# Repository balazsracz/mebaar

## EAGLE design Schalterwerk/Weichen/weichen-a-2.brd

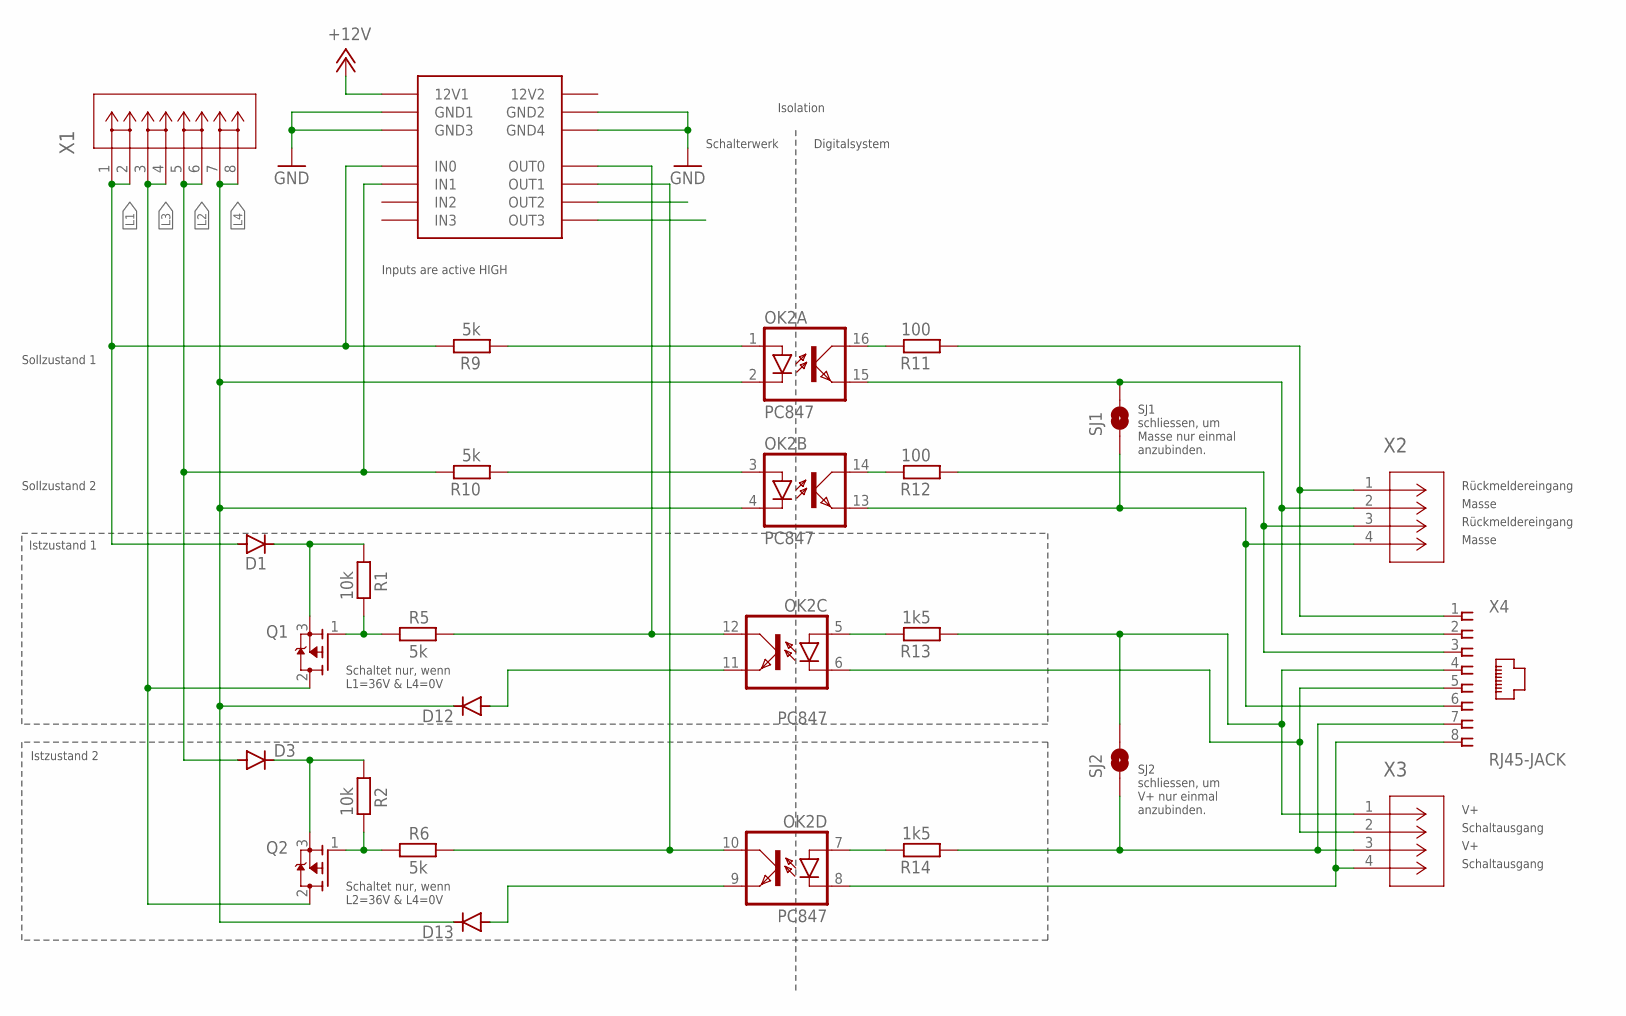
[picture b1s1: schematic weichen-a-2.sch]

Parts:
D1, D3: DIODE-DO214AC; DO214AC
D12, D13: DIODE-MINIMELF; MINIMELF
OK2: PC847; DIL16
Q1, Q2: P-MOSFET; DPAK-2
R1, R2: 10k; R0805
R5, R6, R9, R10: 5k; R0805
R11, R12: 100; R0805
R13, R14: 1k5; R0805
SJ1, SJ2: SJRND2; SJ_RND2
X1: PHNX_4P_508CONN_1017493; PHNX_4P_508
X2, X3: PHNX_4P_350CONN_1984989_PXC; PHNX_4P_350
X4: RJ45-JACK; RJ45-PULSE-E5J88
X5: IO-HAT; IOBOARD

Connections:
12V2: X5.P$22 (12V2)
+12V: X5.P$1 (12V1)
GND: X5.P$2 (GND1), X5.P$11 (GND3), X5.P$12 (GND4), X5.P$21 (GND2)
L1: D1.A, R9.2, X1.1, X1.2, X5.P$3 (IN0)
L2: D3.A, R10.2, X1.5, X1.6, X5.P$4 (IN1)
L3: Q1.2 (D), Q2.2 (D), X1.3, X1.4
L4: D12.C, D13.C, OK2.2 (C), OK2.4 (C), X1.7, X1.8
unnamed: D3.C, Q2.3 (S), R2.1
unnamed: OK2.1 (A), R9.1
unnamed: R11.1, X2.1, X4.1
unnamed: OK2.15 (EMIT), SJ1.P$2 (2), X2.2, X4.2
unnamed: OK2.5 (A), R13.2
unnamed: R12.1, X2.3, X4.3
unnamed: OK2.3 (A), R10.1
unnamed: OK2.7 (A), R14.2
unnamed: Q1.1 (G), R1.2, R5.1
unnamed: Q2.1 (G), R2.2, R6.1
unnamed: D1.C, Q1.3 (S), R1.1
unnamed: OK2.6 (C), X3.2, X4.5
unnamed: OK2.12 (COL), R5.2, X5.P$20 (OUT0)
unnamed: OK2.10 (COL), R6.2, X5.P$19 (OUT1)
unnamed: D12.A, OK2.11 (EMIT)
unnamed: OK2.16 (COL), R11.2
unnamed: OK2.13 (EMIT), SJ1.P$1 (1), X2.4, X4.6
unnamed: OK2.14 (COL), R12.2
unnamed: D13.A, OK2.9 (EMIT)
unnamed: R13.1, SJ2.P$2 (2), X3.1, X4.4
unnamed: R14.1, SJ2.P$1 (1), X3.3, X4.7
unnamed: OK2.8 (C), X3.4, X4.8

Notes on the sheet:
Rückmeldereingang
Masse
Schaltausgang
SJ1 schliessen, um Masse nur einmal anzubinden.
Isolation
Schalterwerk
Digitalsystem
Schaltet nur, wenn L1=36V & L4=0V
Schaltet nur, wenn L2=36V & L4=0V
Sollzustand 1
Sollzustand 2
Istzustand 1
Istzustand 2
SJ2 schliessen, um V+ nur einmal anzubinden.
Inputs are active HIGH

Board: 2 copper layers, 24 parts (0 on the bottom side), 27 nets, no tracks yet.

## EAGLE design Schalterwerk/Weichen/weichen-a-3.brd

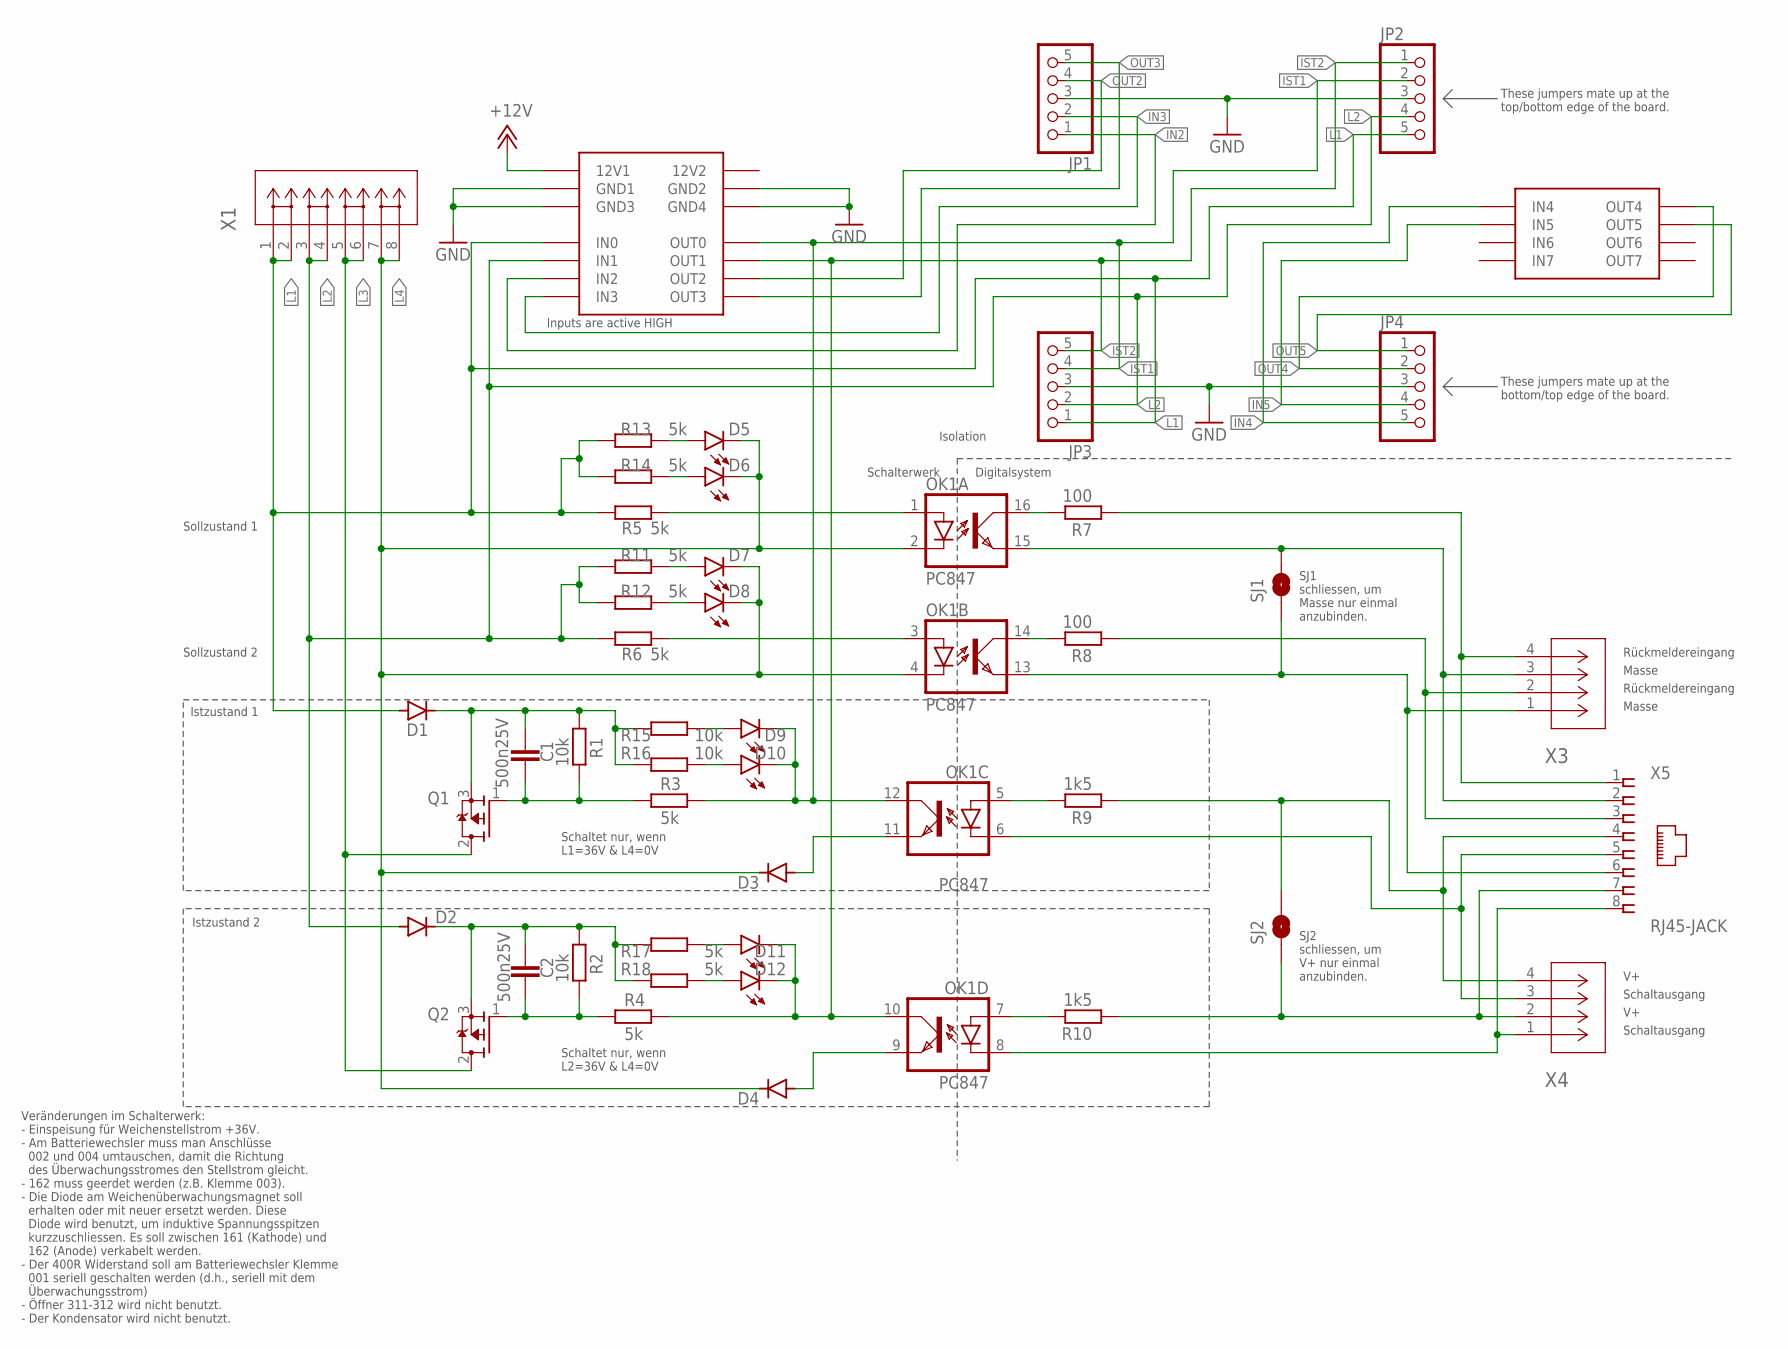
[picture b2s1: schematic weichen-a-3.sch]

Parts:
C1, C2: 500n25V; C0805
D1, D2: DIODE-DO214AC; DO214AC
D3, D4: DIODE-MINIMELF; MINIMELF
D5, D7, D9, D11: LEDCHIPLED_0603; CHIPLED_0603
D6, D8, D10, D12: LEDHEADER
JP1, JP2, JP3, JP4: PINHD-1X55X2MM; 1_05X2MM
OK1: PC847; DIL16
Q1, Q2: P-MOSFET; DPAK-2
R1, R2, R15, R16: 10k; R0805
R3, R4, R5, R6, R11, R12, R13, R14, R17, R18: 5k; R0805
R7, R8: 100; R0805
R9, R10: 1k5; R0805
SJ1, SJ2: SJRND2; SJ_RND2
X1: PHNX_4P_508CONN_1017493; PHNX_4P_508
X2: IO-HAT; IOBOARD
X3, X4: PHNX_4P_350CONN_1984989_PXC; PHNX_4P_350
X5: RJ45-JACK; RJ45-PULSE-E5J88

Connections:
12V2: X2.P$22 (12V2)
+12V: X2.P$1 (12V1)
GND: JP1.3, JP2.3, JP3.3, JP4.3, X2.P$2 (GND1), X2.P$11 (GND3), X2.P$12 (GND4), X2.P$21 (GND2)
IN2: JP1.1, X2.P$5 (IN2)
IN3: JP1.2, X2.P$6 (IN3)
IN4: JP4.5, X2.P$7 (IN4)
IN5: JP4.4, X2.P$8 (IN5)
IST1: D9.C, D10.C, JP2.2, JP3.4, OK1.12 (COL), R3.2, X2.P$20 (OUT0)
IST2: D11.C, D12.C, JP2.1, JP3.5, OK1.10 (COL), R4.2, X2.P$19 (OUT1)
L1: D1.A, JP2.5, JP3.1, R5.2, R13.2, R14.2, X1.1, X1.2, X2.P$3 (IN0)
L2: D2.A, JP2.4, JP3.2, R6.2, R11.2, R12.2, X1.3, X1.4, X2.P$4 (IN1)
L3: Q1.2 (D), Q2.2 (D), X1.5, X1.6
L4: D3.C, D4.C, D5.C, D6.C, D7.C, D8.C, OK1.2 (C), OK1.4 (C), X1.7, X1.8
unnamed: C2.1, D2.C, Q2.3 (S), R2.1, R17.2, R18.2
unnamed: OK1.1 (A), R5.1
unnamed: D7.A, R11.1
unnamed: D5.A, R13.1
unnamed: OK1.5 (A), R9.2
unnamed: D6.A, R14.1
unnamed: OK1.3 (A), R6.1
unnamed: OK1.7 (A), R10.2
unnamed: D8.A, R12.1
unnamed: D9.A, R15.1
unnamed: C2.2, Q2.1 (G), R2.2, R4.1
unnamed: C1.1, D1.C, Q1.3 (S), R1.1, R15.2, R16.2
unnamed: D10.A, R16.1
unnamed: D3.A, OK1.11 (EMIT)
unnamed: D11.A, R17.1
unnamed: OK1.16 (COL), R7.2
unnamed: D12.A, R18.1
unnamed: OK1.14 (COL), R8.2
unnamed: D4.A, OK1.9 (EMIT)
unnamed: C1.2, Q1.1 (G), R1.2, R3.1
NX41: R7.1, X3.4, X5.1
NX42: OK1.15 (EMIT), SJ1.P$2 (2), X3.3, X5.2
NX43: R8.1, X3.2, X5.3
NX44: R9.1, SJ2.P$2 (2), X4.4, X5.4
NX45: OK1.6 (C), X4.3, X5.5
NX46: OK1.13 (EMIT), SJ1.P$1 (1), X3.1, X5.6
NX47: R10.1, SJ2.P$1 (1), X4.2, X5.7
NX48: OK1.8 (C), X4.1, X5.8
OUT2: JP1.4, X2.P$18 (OUT2)
OUT3: JP1.5, X2.P$17 (OUT3)
OUT4: JP4.2, X2.P$16 (OUT4)
OUT5: JP4.1, X2.P$15 (OUT5)

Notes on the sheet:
Rückmeldereingang
Masse
Schaltausgang
SJ1 schliessen, um Masse nur einmal anzubinden.
Isolation
Schalterwerk
Digitalsystem
Schaltet nur, wenn L1=36V & L4=0V
Schaltet nur, wenn L2=36V & L4=0V
Sollzustand 1
Sollzustand 2
Istzustand 1
Istzustand 2
SJ2 schliessen, um V+ nur einmal anzubinden.
Inputs are active HIGH
These jumpers mate up at the top/bottom edge of the board.
These jumpers mate up at the bottom/top edge of the board.
Veränderungen im Schalterwerk: - Einspeisung für Weichenstellstrom +36V. - Am Batteriewechsler muss man Anschlüsse 002 und 004 umtauschen, damit die Richtung des Überwachungsstromes den Stellstrom gleicht. - 162 muss geerdet werden (z.B. Klemme 003). - Die Diode am Weichenüberwachungsmagnet soll er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

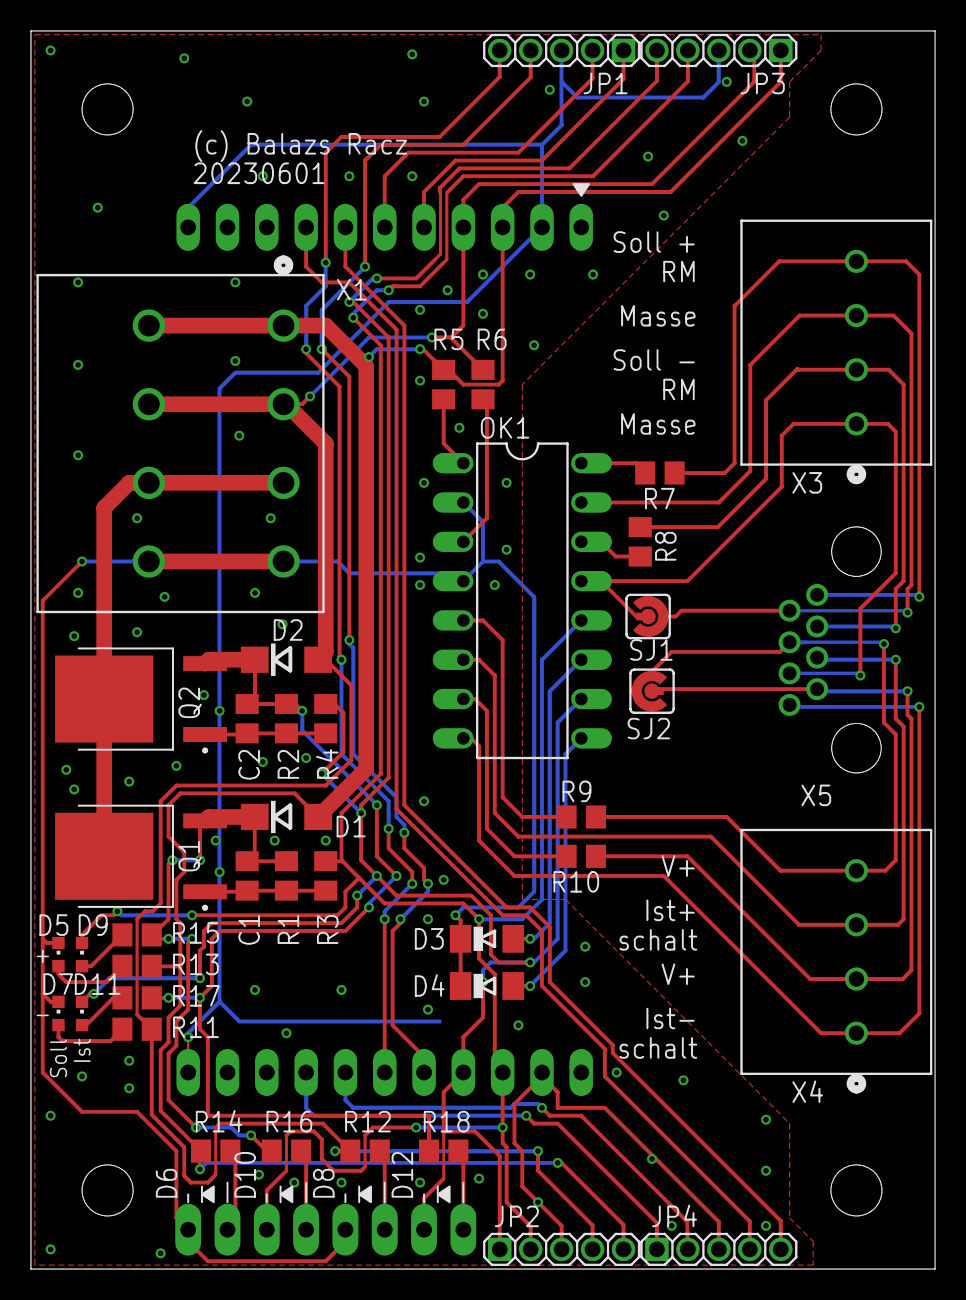
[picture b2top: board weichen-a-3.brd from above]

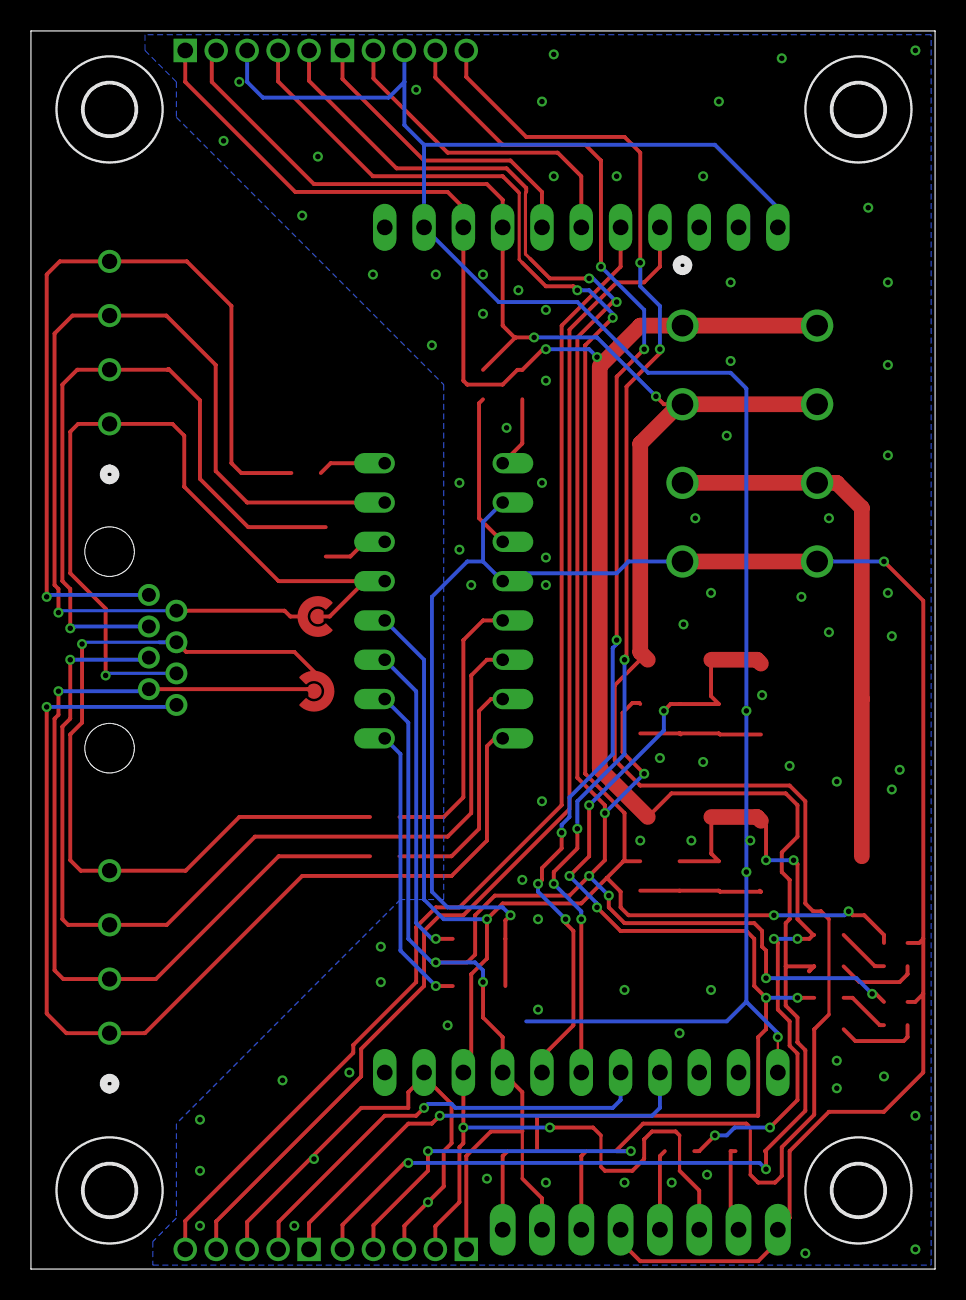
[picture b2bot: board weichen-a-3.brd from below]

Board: 2 copper layers, 58.4 x 80.0 mm, 50 parts (4 on the bottom side), 43 nets.

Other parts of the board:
H1, H2, H3, H4: MOUNT-HOLE3.3; 3,3

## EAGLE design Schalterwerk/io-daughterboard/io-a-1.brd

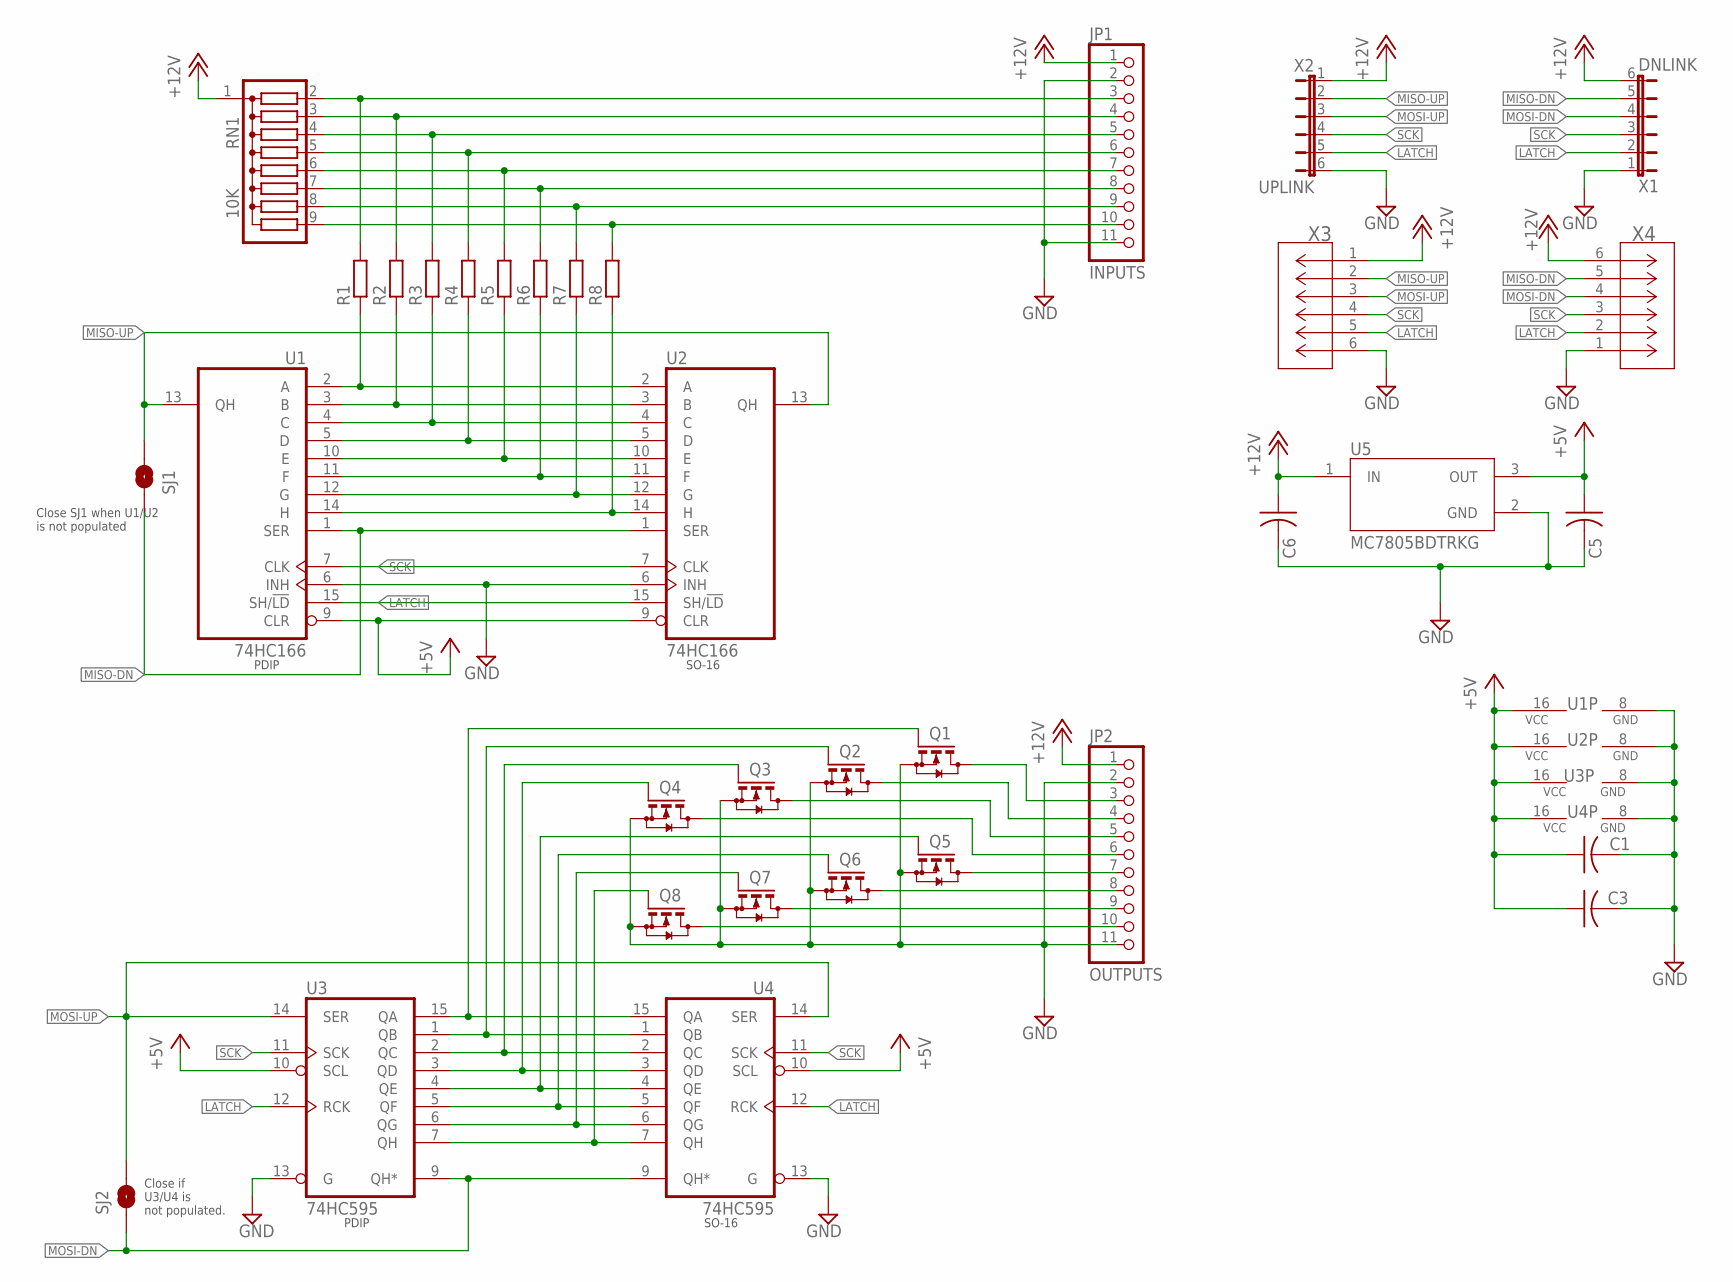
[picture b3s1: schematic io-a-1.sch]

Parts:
C1, C3, C5, C6: C-USC0805; C0805
JP1: INPUTS; 1X11
JP2: OUTPUTS; 1X11
Q1, Q2, Q3, Q4, Q5, Q6, Q7, Q8: BSS123; SOT23
R1, R2, R3, R4, R5, R6, R7, R8: R-EU_R0805; R0805
RN1: 10K; SIL9
SJ1, SJ2: SJRND2; SJ_RND2
U1: 74HC166; DIL16
U2: 74HC166; SO16
U3: 74HC595; DIL16
U4: 74HC595; SO16
U5: MC7805BDTRKG; DPAK229P990X238-4N
X1: DNLINK; JP6F
X2: UPLINK; JP6F-FEM
X3, X4: MOLEX_530470610CON_530470610_MOL; CON_530470610_MOL

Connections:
+5V: C1.1, C3.1, C5.1, U1.9 (CLR), U1.16 (VCC), U2.9 (CLR), U2.16 (VCC), U3.10 (SCL), U3.16 (VCC), U4.10 (SCL), U4.16 (VCC), U5.3 (OUT)
GND: C1.2, C3.2, C5.2, C6.2, JP1.2, JP1.11, JP2.2, JP2.11, Q1.2 (S), Q2.2 (S), Q3.2 (S), Q4.2 (S), Q5.2 (S), Q6.2 (S), Q7.2 (S), Q8.2 (S), U1.6 (INH), U1.8 (GND), U2.6 (INH), U2.8 (GND), U3.8 (GND), U3.13 (G), U4.8 (GND), U4.13 (G), U5.2 (GND), X1.1, X2.6, X3.6, X4.1; also elsewhere on the board
LATCH: U1.15 (SH/!LD), U2.15 (SH/!LD), U3.12 (RCK), U4.12 (RCK), X1.2, X2.5, X3.5, X4.2
MISO-DN: SJ1.P$1 (1), U1.1 (SER), U2.1 (SER), X1.5, X4.5
MISO-UP: SJ1.P$2 (2), U1.13 (QH), U2.13 (QH), X2.2, X3.2
MOSI-DN: SJ2.P$1 (1), U3.9 (QH*), U4.9 (QH*), X1.4, X4.4
MOSI-UP: SJ2.P$2 (2), U3.14 (SER), U4.14 (SER), X2.3, X3.3
unnamed: JP2.6, Q4.3 (D)
unnamed: JP2.5, Q3.3 (D)
unnamed: JP2.4, Q2.3 (D)
unnamed: JP2.3, Q1.3 (D)
unnamed: JP1.3, R1.2, RN1.2
unnamed: JP1.4, R2.2, RN1.3
unnamed: JP1.5, R3.2, RN1.4
unnamed: JP1.6, R4.2, RN1.5
unnamed: JP1.7, R5.2, RN1.6
unnamed: JP1.8, R6.2, RN1.7
unnamed: JP1.9, R7.2, RN1.8
unnamed: JP1.10, R8.2, RN1.9
unnamed: JP2.7, Q5.3 (D)
unnamed: JP2.8, Q6.3 (D)
unnamed: JP2.9, Q7.3 (D)
unnamed: JP2.10, Q8.3 (D)
PA: Q1.1 (G), U3.15 (QA), U4.15 (QA)
PB: Q2.1 (G), U3.1 (QB), U4.1 (QB)
PC: Q3.1 (G), U3.2 (QC), U4.2 (QC)
PD: Q4.1 (G), U3.3 (QD), U4.3 (QD)
PE: Q5.1 (G), U3.4 (QE), U4.4 (QE)
PF: Q6.1 (G), U3.5 (QF), U4.5 (QF)
PG: Q7.1 (G), U3.6 (QG), U4.6 (QG)
PH: Q8.1 (G), U3.7 (QH), U4.7 (QH)
QA: R1.1, U1.2 (A), U2.2 (A)
QB: R2.1, U1.3 (B), U2.3 (B)
QC: R3.1, U1.4 (C), U2.4 (C)
QD: R4.1, U1.5 (D), U2.5 (D)
QE: R5.1, U1.10 (E), U2.10 (E)
QF: R6.1, U1.11 (F), U2.11 (F)
QG: R7.1, U1.12 (G), U2.12 (G)
QH: R8.1, U1.14 (H), U2.14 (H)
SCK: U1.7 (CLK), U2.7 (CLK), U3.11 (SCK), U4.11 (SCK), X1.3, X2.4, X3.4, X4.3

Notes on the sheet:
Close SJ1 when U1/U2 is not populated
Close if U3/U4 is not populated.
PDIP
SO-16

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
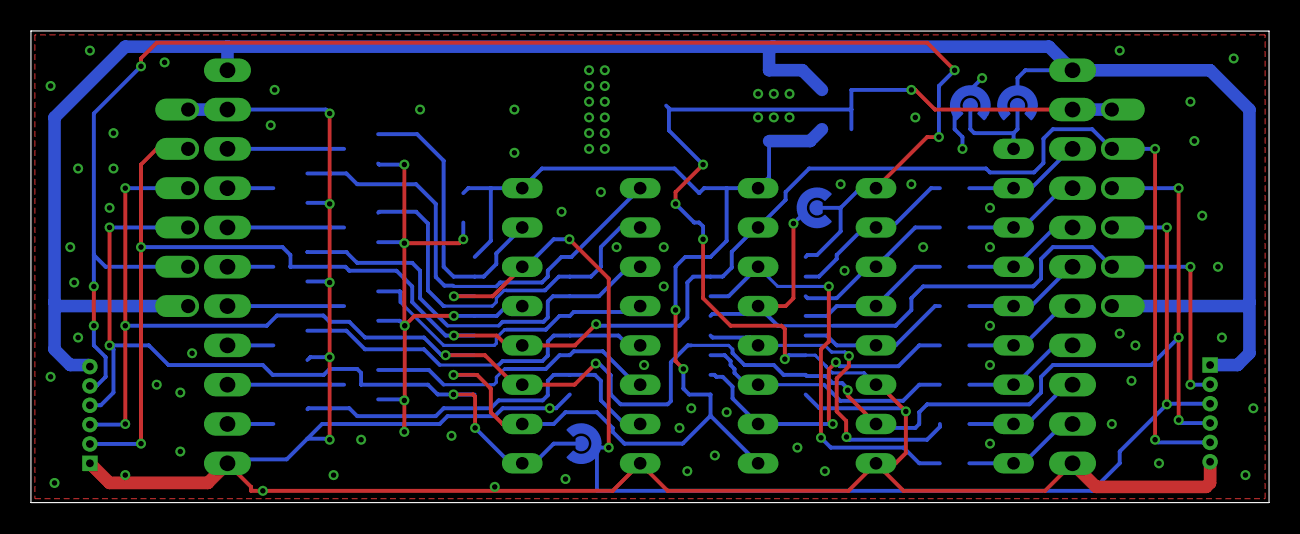
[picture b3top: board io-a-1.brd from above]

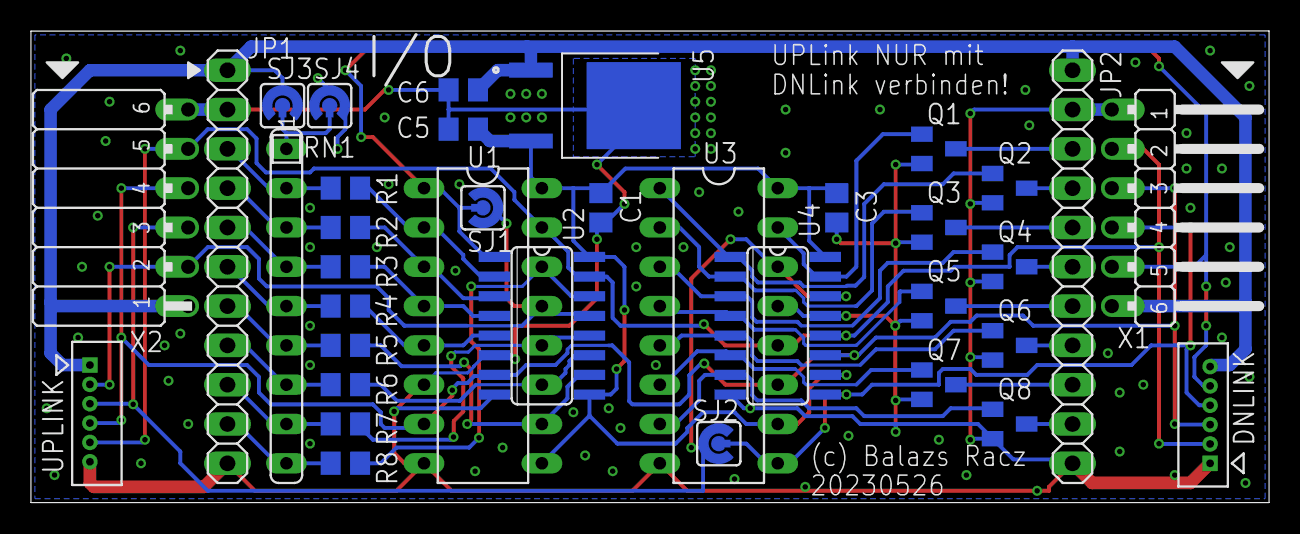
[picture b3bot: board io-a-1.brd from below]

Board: 2 copper layers, 80.0 x 30.5 mm, 36 parts (36 on the bottom side), 42 nets.

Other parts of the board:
SJ3, SJ4: SJ_RND2

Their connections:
GND: SJ4.P$2; also elsewhere on the board

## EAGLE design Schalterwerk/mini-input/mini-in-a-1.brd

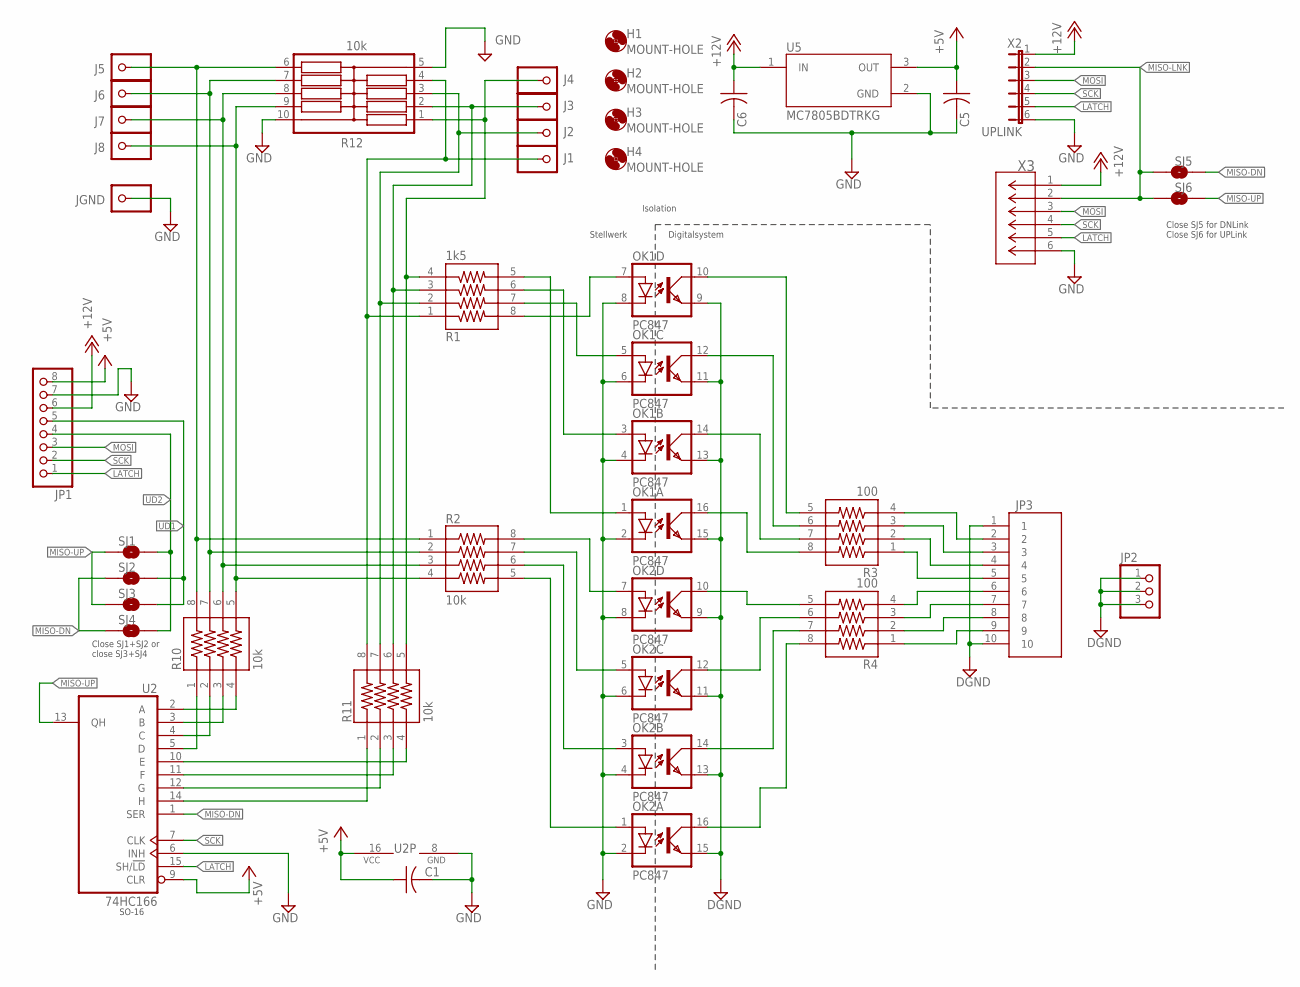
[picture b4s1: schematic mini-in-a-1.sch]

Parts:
C1, C5, C6: C-USC0805; C0805
H1, H2, H3, H4: MOUNT-HOLE; MOUNT-HOLE-2,8
J1, J2, J3, J4, J5, J6, J7, J8: LARGE-SOLDERPADWITH-HOLE; LARGE-SOLDERPAD-WITH-HOLES
JGND: LARGE-SOLDERPADWITH-HOLE; LARGE-SOLDERPAD-WITH-HOLES
JP1: PINHD-1X8; 1X08
JP2: PINHD-1X3; 1X03
JP3: TE-CON-MTA150-RA-HEADER-1-640457-0; TE_1-640457-0
OK1, OK2: PC847; DIL16
R1: 1k5; RESCAXS127P508X320X70-8N
R2, R10, R11: 10k; RESCAXS127P508X320X70-8N
R3, R4: 100; RESCAXS127P508X320X70-8N
R12: 10k; RESCAV127P640X310X70-10N
SJ1, SJ2, SJ3, SJ4, SJ5, SJ6: SJRND2; SJ_RND2
U2: 74HC166; SO16
U5: MC7805BDTRKG; DPAK229P990X238-4N
X2: UPLINK; JP6F-FEM
X3: MOLEX_530480610CON_530480610_MOL; CON_530480610_MOL

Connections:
+5V: C1.1, C5.1, JP1.8, U2.9 (CLR), U2.16 (VCC), U5.3 (OUT)
+12V: C6.1, JP1.6, U5.1 (IN), X2.1, X3.1
DGND: JP2.1, JP2.2, JP2.3, JP3.1, JP3.10, OK1.9 (EMIT), OK1.11 (EMIT), OK1.13 (EMIT), OK1.15 (EMIT), OK2.9 (EMIT), OK2.11 (EMIT), OK2.13 (EMIT), OK2.15 (EMIT)
GND: C1.2, C5.2, C6.2, JGND.P$1, JP1.7, OK1.2 (C), OK1.4 (C), OK1.6 (C), OK1.8 (C), OK2.2 (C), OK2.4 (C), OK2.6 (C), OK2.8 (C), R12.5, R12.10, U2.6 (INH), U2.8 (GND), U5.2 (GND), X2.6, X3.6
LATCH: JP1.1, U2.15 (SH/!LD), X2.5, X3.5
MISO-DN: SJ2.P$1 (1), SJ4.P$1 (1), SJ5.P$1 (1), U2.1 (SER)
MISO-LNK: SJ5.P$2 (2), SJ6.P$2 (2), X2.2, X3.2
MISO-UP: SJ1.P$1 (1), SJ3.P$1 (1), SJ6.P$1 (1), U2.13 (QH)
MOSI: JP1.3, X2.3, X3.3
unnamed: J1.P$1, R1.1, R11.8, R12.4
unnamed: J2.P$1, R1.2, R11.7, R12.3
unnamed: J3.P$1, R1.3, R11.6, R12.2
unnamed: J4.P$1, R1.4, R11.5, R12.1
unnamed: J5.P$1, R2.1, R10.8, R12.6
unnamed: J6.P$1, R2.2, R10.7, R12.7
unnamed: J7.P$1, R2.3, R10.6, R12.8
unnamed: J8.P$1, R2.4, R10.5, R12.9
unnamed: OK1.7 (A), R1.8
unnamed: OK1.5 (A), R1.7
unnamed: OK1.3 (A), R1.6
unnamed: OK1.1 (A), R1.5
unnamed: JP3.2, R3.4
unnamed: JP3.3, R3.3
unnamed: JP3.4, R3.2
unnamed: JP3.5, R3.1
unnamed: JP3.6, R4.4
unnamed: JP3.7, R4.3
unnamed: JP3.8, R4.2
unnamed: JP3.9, R4.1
unnamed: OK1.10 (COL), R3.5
unnamed: OK1.12 (COL), R3.6
unnamed: OK1.14 (COL), R3.7
unnamed: OK1.16 (COL), R3.8
unnamed: OK2.10 (COL), R4.5
unnamed: OK2.12 (COL), R4.6
unnamed: OK2.14 (COL), R4.7
unnamed: OK2.16 (COL), R4.8
unnamed: OK2.7 (A), R2.8
unnamed: OK2.5 (A), R2.7
unnamed: OK2.3 (A), R2.6
unnamed: OK2.1 (A), R2.5
QA: R10.4, U2.2 (A)
QB: R10.3, U2.3 (B)
QC: R10.2, U2.4 (C)
QD: R10.1, U2.5 (D)
QE: R11.4, U2.10 (E)
QF: R11.3, U2.11 (F)
QG: R11.2, U2.12 (G)
QH: R11.1, U2.14 (H)
SCK: JP1.2, U2.7 (CLK), X2.4, X3.4
UD1: JP1.5, SJ2.P$2 (2), SJ3.P$2 (2)
UD2: JP1.4, SJ1.P$2 (2), SJ4.P$2 (2)

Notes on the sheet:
SO-16
Isolation
Digitalsystem
Close SJ1+SJ2 or close SJ3+SJ4
Stellwerk
Close SJ5 for DNLink Close SJ6 for UPLink

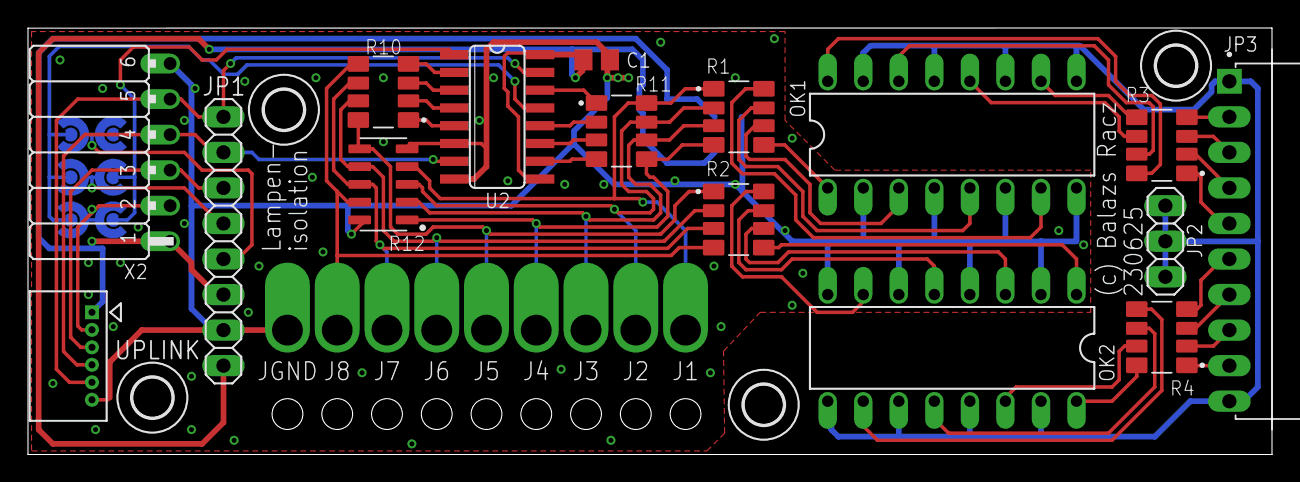
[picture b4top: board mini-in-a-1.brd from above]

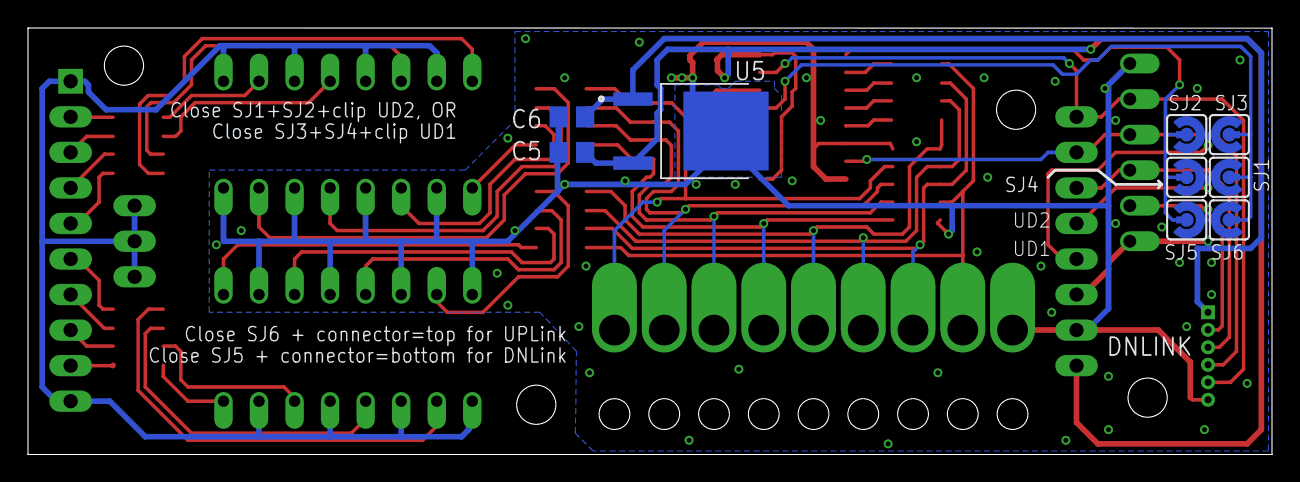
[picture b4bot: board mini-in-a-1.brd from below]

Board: 2 copper layers, 88.9 x 30.5 mm, 38 parts (9 on the bottom side), 52 nets.

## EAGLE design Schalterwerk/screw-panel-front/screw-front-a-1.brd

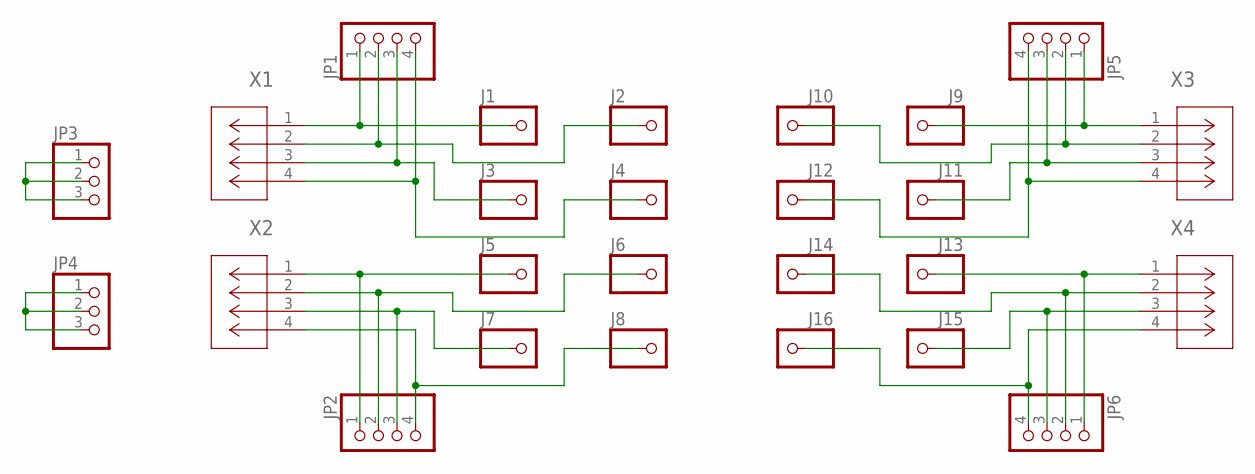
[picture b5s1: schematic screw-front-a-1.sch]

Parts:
J1, J2, J3, J4, J5, J6, J7, J8, J9, J10, J11, J12, J13, J14, J15, J16: M4-SCREW-HOLE
JP1, JP2, JP5, JP6: PINHD-1X4; 1X04
JP3, JP4: PINHD-1X3; 1X03
X1, X2, X3, X4: PHNX_4P_350CONN_1984989_PXC; PHNX_4P_350

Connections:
unnamed: J1.P$1, JP1.1, X1.1
unnamed: J2.P$1, JP1.2, X1.2
unnamed: J3.P$1, JP1.3, X1.3
unnamed: J4.P$1, JP1.4, X1.4
unnamed: J5.P$1, JP2.1, X2.1
unnamed: J6.P$1, JP2.2, X2.2
unnamed: J7.P$1, JP2.3, X2.3
unnamed: J8.P$1, JP2.4, X2.4
unnamed: JP3.1, JP3.2, JP3.3
unnamed: JP4.1, JP4.2, JP4.3
unnamed: J9.P$1, JP5.1, X3.1
unnamed: J10.P$1, JP5.2, X3.2
unnamed: J11.P$1, JP5.3, X3.3
unnamed: J12.P$1, JP5.4, X3.4
unnamed: J13.P$1, JP6.1, X4.1
unnamed: J14.P$1, JP6.2, X4.2
unnamed: J15.P$1, JP6.3, X4.3
unnamed: J16.P$1, JP6.4, X4.4

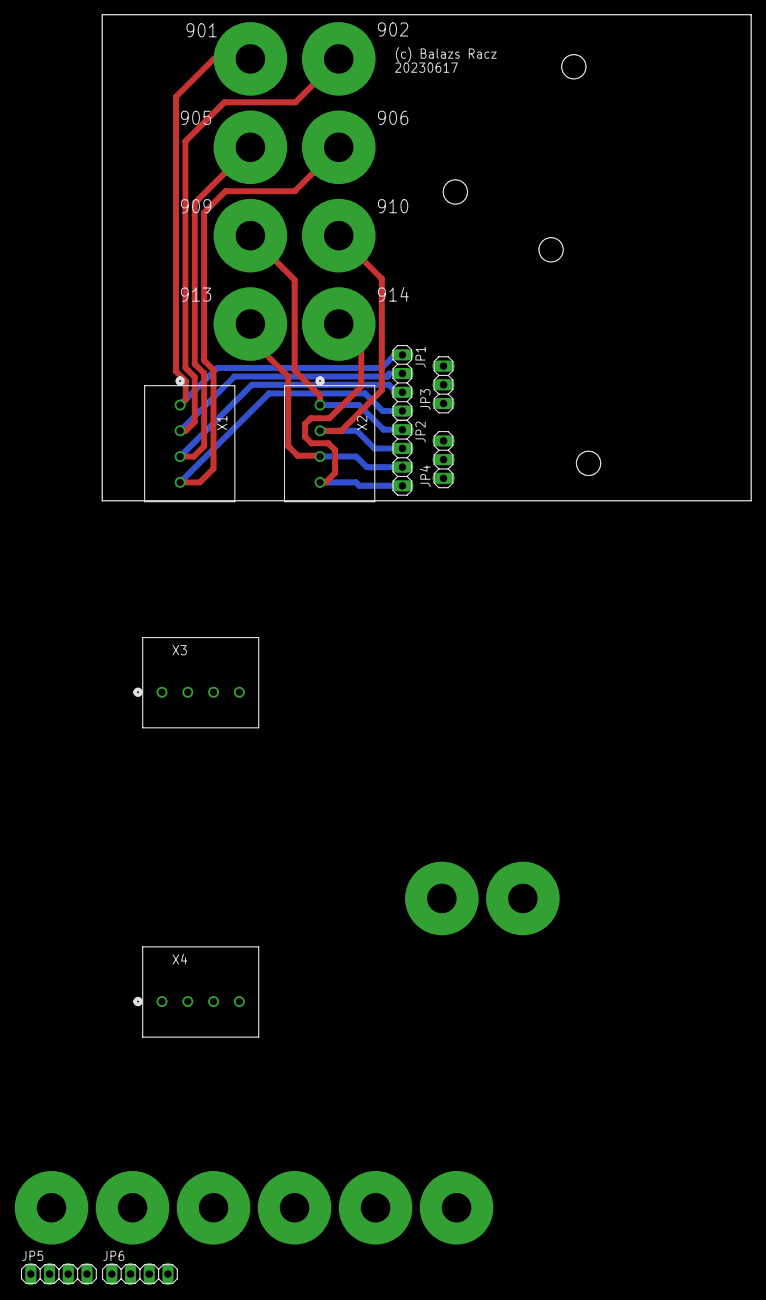
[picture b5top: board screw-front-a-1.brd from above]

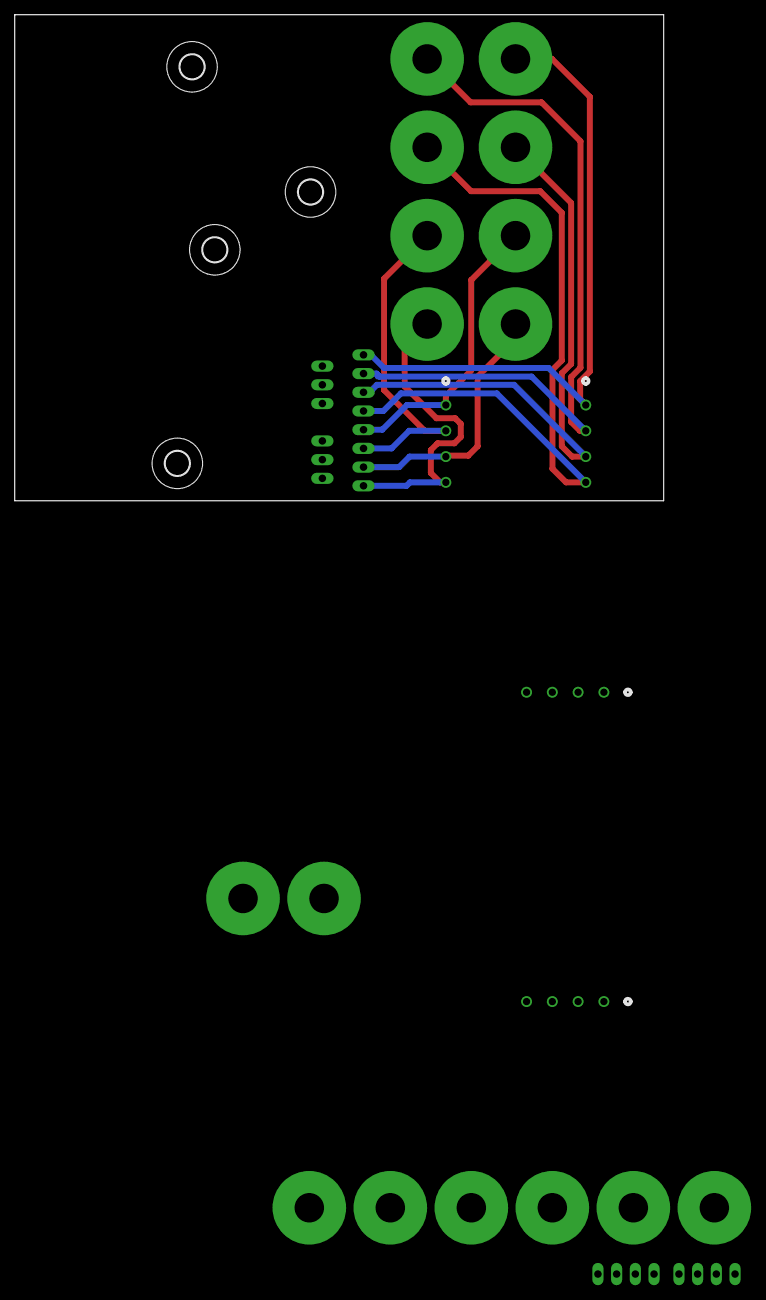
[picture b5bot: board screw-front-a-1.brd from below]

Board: 2 copper layers, 88.1 x 66.0 mm, 30 parts (4 on the bottom side), 18 nets.

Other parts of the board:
H1, H2, H3, H4: MOUNT-HOLE3.3; 3,3

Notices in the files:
Schalterwerk/Weichen/weichen-a-2.sch:
LICENSE: Licensed by the Solderpad Hardware License V2.0
parts and their libraries:
COPYRIGHT: Copyright (C) 2023 Ultra Librarian. All rights reserved.
